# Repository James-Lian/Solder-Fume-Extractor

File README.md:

# 💨 Solder-Fume-Extractor
A small solder fume extractor complete with an air quality sensor for hobbyist soldering applications. Soldering can get pretty fume-y (pun intended), irritating the eyes, nose, and throat. While this extractor won't be as good as a commercial-grade fume hood, the filter will at least mitigate some of solder smoke. 
<br>
<br>
Encompasses a control board with the air quality sensor, a 12V PC fan, activated carbon filter, and custom-designed 3d-printed casing to house everything. 
<br>
<br>
Stardance Project Tracker (Devlogs): [https://stardance.hackclub.com/projects/36238](https://stardance.hackclub.com/projects/36238)

## 💡 Features
- powered by a [12V DC power supply](https://www.amazon.ca/dp/B09W8S3FBV)
- 0.91inch OLED SSD1306
- LM2596-3.3 buck converter for 3V3 supply
- ENS160+AHT21 sensor to detect VOCs and eCO2
- ESP-01S microcontroller
- custom 3d-printed casing
- [12V desk fan](https://www.amazon.ca/dp/B0DPWWMNYM) which pulls solder fumes through an [activated carbon filter](https://www.amazon.ca/dp/B0DVX29MLH?ref=ppx_yo2ov_dt_b_fed_asin_title)
- flip flop switch circuit + MOSFET to control the fan, flyback diode to prevent MOSFET damage

## 📄 PCB & Schematic

<br>
<br>
Note: additional space is intentionally left empty at the bottom left of the PCB to leave space for the sensor components.

## 🧱 CAD Model
The casing for both the controller board and desk fan were designed in Fusion360. The casing for the controller board covers all the components apart from the air quality sensor, which, of course, needs ample exposure to the air to make an accurate reading. 

## ⚙️ Assembly
1. Download the production files from the production folder and upload them to a manufacturer like JLCPCB
2. Upload the code to the ESP-01S through something like the [CP2102 module](https://www.amazon.ca/dp/B07D6LLX19)
3. After acquiring the PCB, solder all the components to the board. Ensure you leave enough spacing between the PCB and the [right-angle male headers](https://www.amazon.ca/dp/B01461DQ6S?ref=ppx_yo2ov_dt_b_fed_asin_title) for the fan's female connectors to fit.
4. The fan's casing is in three parts. Add heatset inserts to the thickest part, and then sandwich your activated carbon filter between the two grill frames before assembling all three together with 4 M3 screws.
5. The PCB's controller casing comes with an optional screw hole for secure placement. In my experience, it's not needed.  

## ⌨️ Code + Sensors
The code comes with preventative measures to prevent OLED screen burn in, such as by inverting or scrolling the text, and turning off the screen at times. Do note that the ENS160+AHT21 sensor needs to be (unfortunately) powered on for at least 24 hours (ideally 48) to output accurate readings. 

## 📋 BOM
Here's a list of components for the build (more complete version with links + prices in root repository):
### PCB
| Designator | Footprint | Quantity |
| -------- | -------- | -------- |
| C1 680µF | CP_Radial_D10.0mm_P5.00mm | 1 |
| C2 220µF | CP_Radial_D6.3mm_P2.50mm | 1 |
| C3, C4 0.1µF | 0805 | 2 |
| C5 10nF | 0805 | 1 |
| C6 1µF | 0805 | 1 |
| D1 1N5822 | D_DO-201AD_P15.24mm_Horizontal | 1 |
| D2 1N4001 | D_DO-41_SOD81_P10.16mm_Horizontal | 1 |
| D3, D4 1N4148 | D_DO-35_SOD27_P7.62mm_Horizontal | 2 |
| J1 Barrel_Jack_Switch | XKB_DC-005-5A-2.0 | 1 |
| J2 [Fan](https://www.amazon.ca/dp/B0DPWWMNYM) | [PinHeader_1x03_P2.54mm_Horizontal](https://www.amazon.ca/dp/B01461DQ6S?ref=ppx_yo2ov_dt_b_fed_asin_title) | 1 |
| [Activated Carbon Filter](https://www.amazon.ca/dp/B0DVX29MLH?ref=ppx_yo2ov_dt_b_fed_asin_title) | | 1 |
| [12V DC Power Supply](https://www.amazon.ca/dp/B09W8S3FBV) | | 1 |
| L1 33µH | L_Bourns_SRU5016_5.2x5.2mm | 1 |
| Q1 STP55NF06L | TO-220-3_Vertical | 1 |
| Q2, Q3 PN2222 | TO-92_Inline | 2 |
| R1, R4, R5, R8 10kΩ | R_Axial_DIN0207_L6.3mm_D2.5mm_P7.62mm_Horizontal | 4 |
| R2, R3 1kΩ | R_Axial_DIN0207_L6.3mm_D2.5mm_P7.62mm_Horizontal | 2 |
| R6, R7 100kΩ | R_Axial_DIN0207_L6.3mm_D2.5mm_P7.62mm_Horizontal | 2 |
| SW1 CherryMXSwitch | SW_Cherry_MX_1.00u_PCB | 1 |
| U1 LM2596S-3.3 | TO-263-5_TabPin3 | 1 |
| U2 ESP-01S | PinSocket_2x04_P2.54mm_Vertical | 1 |
| U3 ENS160+AHT21 | PinSocket_1x08_P2.54mm_Vertical | 1 |
| U4 0.91inch SSD1306 OLED | ER_OLEDM0.91_1x-I2C | 1 |

## 🖼️ Final Build Pictures

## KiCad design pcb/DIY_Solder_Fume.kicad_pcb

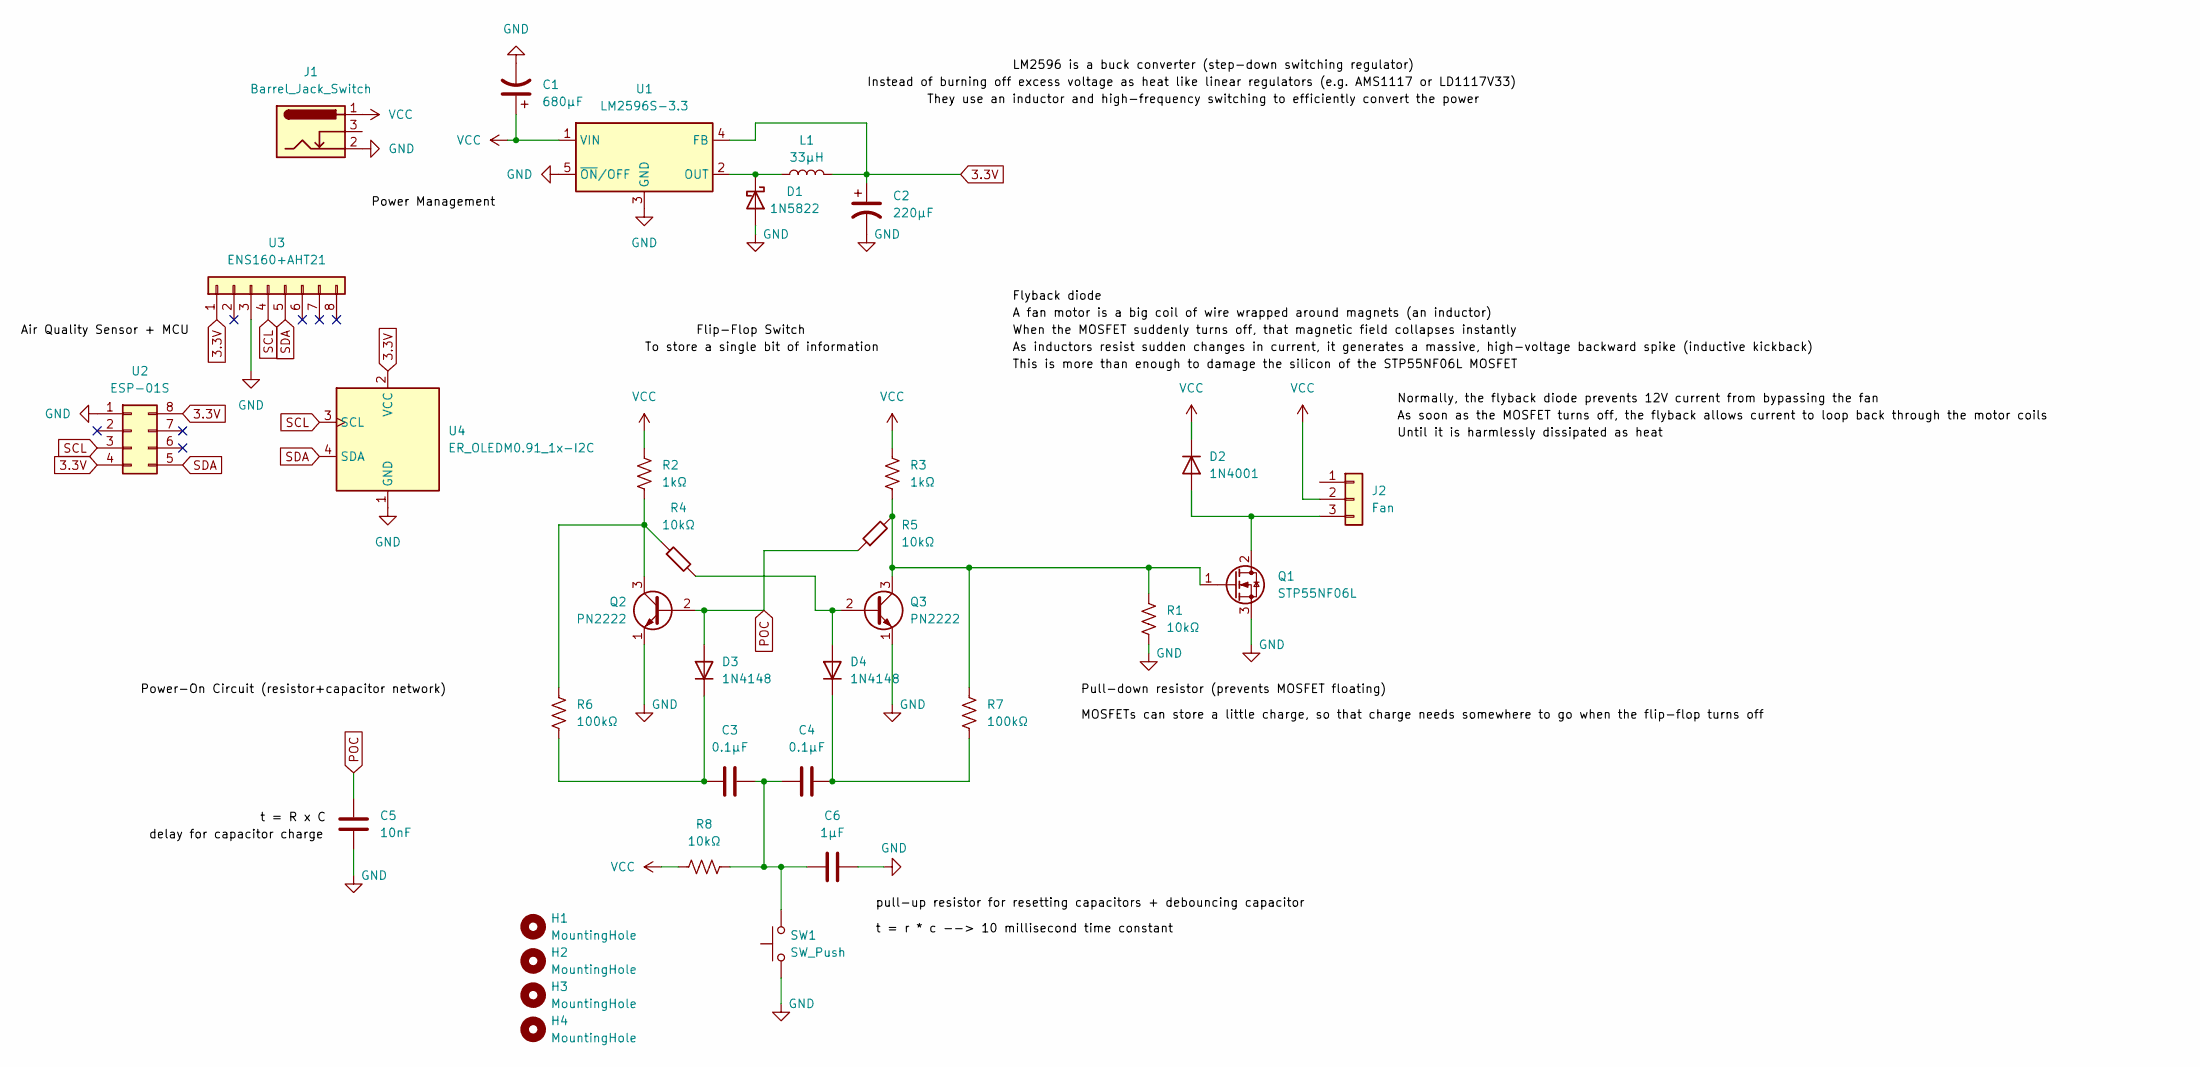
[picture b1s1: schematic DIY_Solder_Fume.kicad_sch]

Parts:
C1: 680µF; CP_Radial_D10.0mm_P5.00mm
C2: 220µF; CP_Radial_D6.3mm_P2.50mm
C3, C4: 0.1µF; C_0805_2012Metric
C5: 10nF; C_0805_2012Metric
C6: 1µF; C_0805_2012Metric
D1: 1N5822; D_DO-201AD_P15.24mm_Horizontal
D2: 1N4001; D_DO-41_SOD81_P10.16mm_Horizontal
D3, D4: 1N4148; D_DO-35_SOD27_P7.62mm_Horizontal
H1, H2, H3, H4: MountingHole; MountingHole_3.2mm_M3_Pad
J1: Barrel_Jack_Switch; XKB_DC-005-5A-2.0
J2: Fan; PinHeader_1x03_P2.54mm_Horizontal
L1: 33µH; L_Bourns_SRU5016_5.2x5.2mm
Q1: STP55NF06L; TO-220-3_Vertical
Q2, Q3: PN2222; TO-92_Inline
R1, R4, R5, R8: 10kΩ; R_Axial_DIN0207_L6.3mm_D2.5mm_P7.62mm_Horizontal
R2, R3: 1kΩ; R_Axial_DIN0207_L6.3mm_D2.5mm_P7.62mm_Horizontal
R6, R7: 100kΩ; R_Axial_DIN0207_L6.3mm_D2.5mm_P7.62mm_Horizontal
SW1: SW_Push; SW_Cherry_MX_1.00u_PCB
U1: LM2596S-3.3; TO-263-5_TabPin3
U2: ESP-01S; PinSocket_2x04_P2.54mm_Vertical
U3: ENS160+AHT21; PinSocket_1x08_P2.54mm_Vertical
U4: ER_OLEDM0.91_1x-I2C

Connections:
3.3V: C2.1, L1.2, U1.4 (FB), U2.4, U2.8, U3.1, U4.2 (VCC)
GND: C1.2, C2.2, C5.1, C6.1, D1.2 (A), J1.2, Q1.3 (S), Q2.1 (E), Q3.1 (E), R1.2, SW1.1, U1.3 (GND), U1.5 (~ON/OFF), U2.1, U3.3, U4.1 (GND)
unnamed: C3.2, C4.2, C6.2, R8.2, SW1.2
unnamed: D1.1 (K), L1.1, U1.2 (OUT)
unnamed: D2.2 (A), J2.3, Q1.2 (D)
unnamed: C3.1, D3.1 (K), R6.2
unnamed: D4.2 (A), Q3.2 (B), R4.2
unnamed: C4.1, D4.1 (K), R7.2
unnamed: Q1.1 (G), Q3.3 (C), R1.1, R3.2, R5.2, R7.1
unnamed: Q2.3 (C), R2.2, R4.1, R6.1
POC: C5.2, D3.2 (A), Q2.2 (B), R5.1
SCL: U2.3, U3.4, U4.3 (SCL)
SDA: U2.5, U3.5, U4.4 (SDA)
VCC: C1.1, D2.1 (K), J1.1, J2.2, R2.1, R3.1, R8.1, U1.1 (VIN)

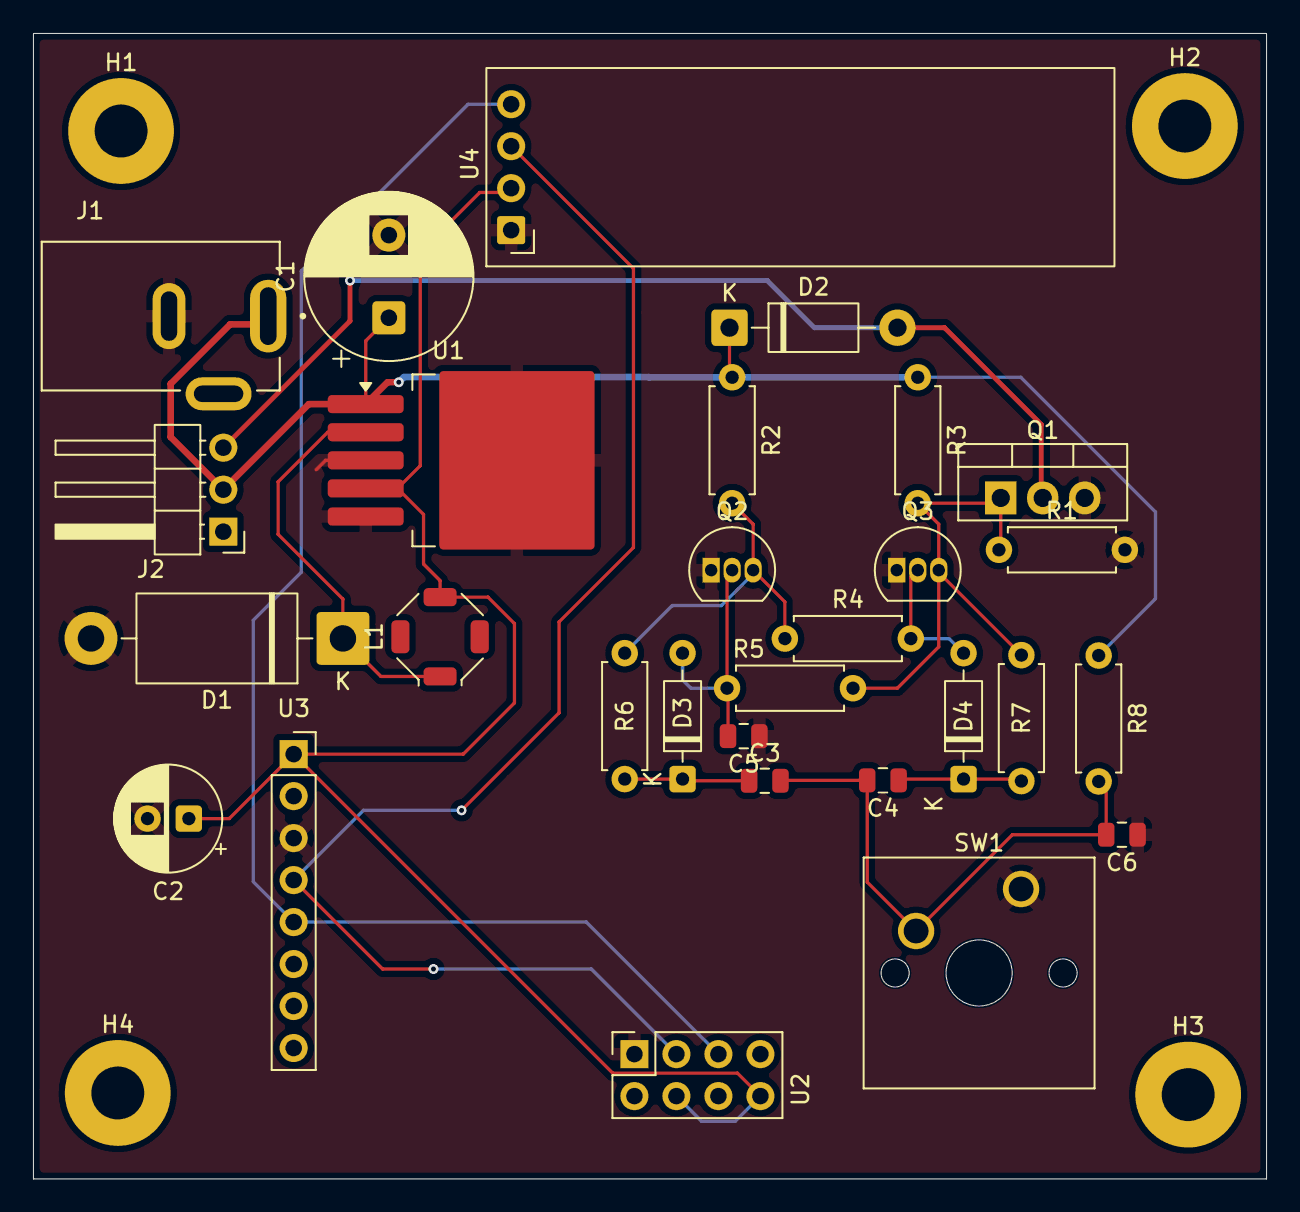
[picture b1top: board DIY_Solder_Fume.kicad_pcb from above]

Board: 2 copper layers, 74.6 x 69.3 mm, 33 parts (0 on the bottom side), 14 nets.

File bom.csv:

Designator,Footprint,Quantity,Value,LCSC Part #
C1,CP_Radial_D10.0mm_P5.00mm,1,680µF,
C2,CP_Radial_D6.3mm_P2.50mm,1,220µF,
"C3, C4",0805,2,0.1µF,
C5,0805,1,10nF,
C6,0805,1,1µF,
D1,D_DO-201AD_P15.24mm_Horizontal,1,1N5822,
D2,D_DO-41_SOD81_P10.16mm_Horizontal,1,1N4001,
"D3, D4",D_DO-35_SOD27_P7.62mm_Horizontal,2,1N4148,
J1,XKB_DC-005-5A-2.0,1,Barrel_Jack_Switch,
J2,PinHeader_1x03_P2.54mm_Horizontal,1,Fan,
L1,L_Bourns_SRU5016_5.2x5.2mm,1,33µH,
Q1,TO-220-3_Vertical,1,STP55NF06L,
"Q2, Q3",TO-92_Inline,2,PN2222,
"R1, R4, R5, R8",R_Axial_DIN0207_L6.3mm_D2.5mm_P7.62mm_Horizontal,4,10kΩ,
"R2, R3",R_Axial_DIN0207_L6.3mm_D2.5mm_P7.62mm_Horizontal,2,1kΩ,
"R6, R7",R_Axial_DIN0207_L6.3mm_D2.5mm_P7.62mm_Horizontal,2,100kΩ,
SW1,SW_Cherry_MX_1.00u_PCB,1,SW_Push,
U1,TO-263-5_TabPin3,1,LM2596S-3.3,
U2,PinSocket_2x04_P2.54mm_Vertical,1,ESP-01S,
U3,PinSocket_1x08_P2.54mm_Vertical,1,ENS160+AHT21,
U4,ER_OLEDM0.91_1x-I2C,1,ER_OLEDM0.91_1x-I2C,
